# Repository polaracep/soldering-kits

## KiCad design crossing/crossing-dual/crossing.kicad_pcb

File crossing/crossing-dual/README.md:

## 2 Mode Level Crossing (přejezd) 

A level crossing sign. based on czech ažd-97. 

### Features 

- 2 selectable operational modes (changeable using solder bridges)
    1) the leds blinking alternately
    2) pad in the middle can be used as a button to turn the leds on
- can be soldered with smd or tht parts.
- a printable leg (M2 screws for mounting)
 
### Mounting

1. On top of the board is a hole for a lanyard/keychain.
2. In the folder `3D addons` are STLs for a leg and hoods for the LEDs. 
    - use an M2 screw
    - No nut is necessary, the leg is made to be a tight fit

### Circuit

[falstad link](https://tinyurl.com/22jwxxro)

the basic circuit is just a basic astable multivibrator with 2 leds. 

the second circuit bypasses the capacitors, instead using a resistive pad and a resistor divider, which pull both bases of the transistors high, thus turning led's on.

you don't need to solder every component for only one of the circuits to work. all parts are labeled with the numbers **1** or **2**, each corresponding to one of the circuits. you can then select the desired one using solder pads.

### Schematic

### PCB + dimensions

### BOM
| REF | CNT | NAME
| --- | ----- | -----
| BT1 | 1 | 2032 Holder
| C1, C2 | 2 | 47uF, 6.3x5
| D1, D2 | 2 | Red LED, 10mm
| Q1, Q2 | 2 | 2N3904, TO-92
| R1, R6 | 2 | 62k, 0207
| R2, R5 | 2 | 100R, 0207
| R3 | 1 | 1M, 0207
| R4 | 1 | 10k, 0207
| SW1 | 1 | 3-Pin, SPDT
| - | - | -
| SUM | 14 | 

#### Disclaimer 
I hereby give up all responsibility for the functionality of your boards.

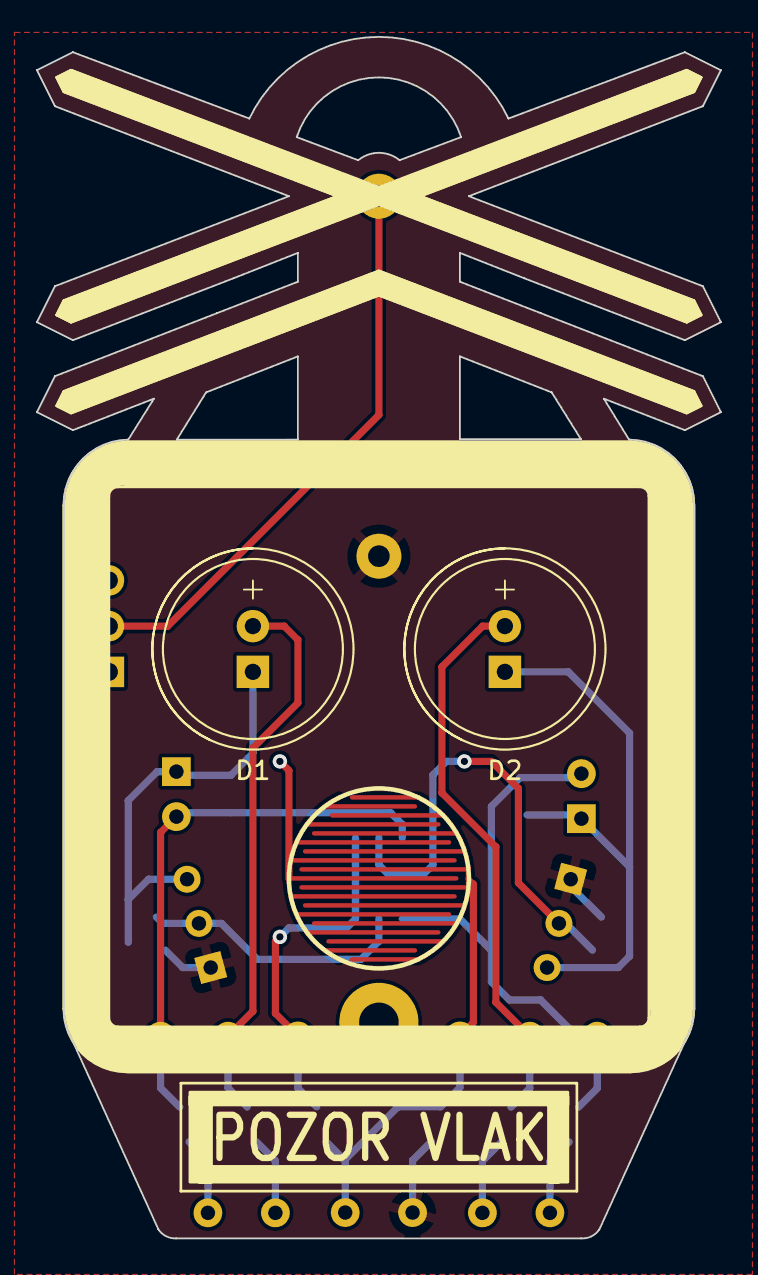
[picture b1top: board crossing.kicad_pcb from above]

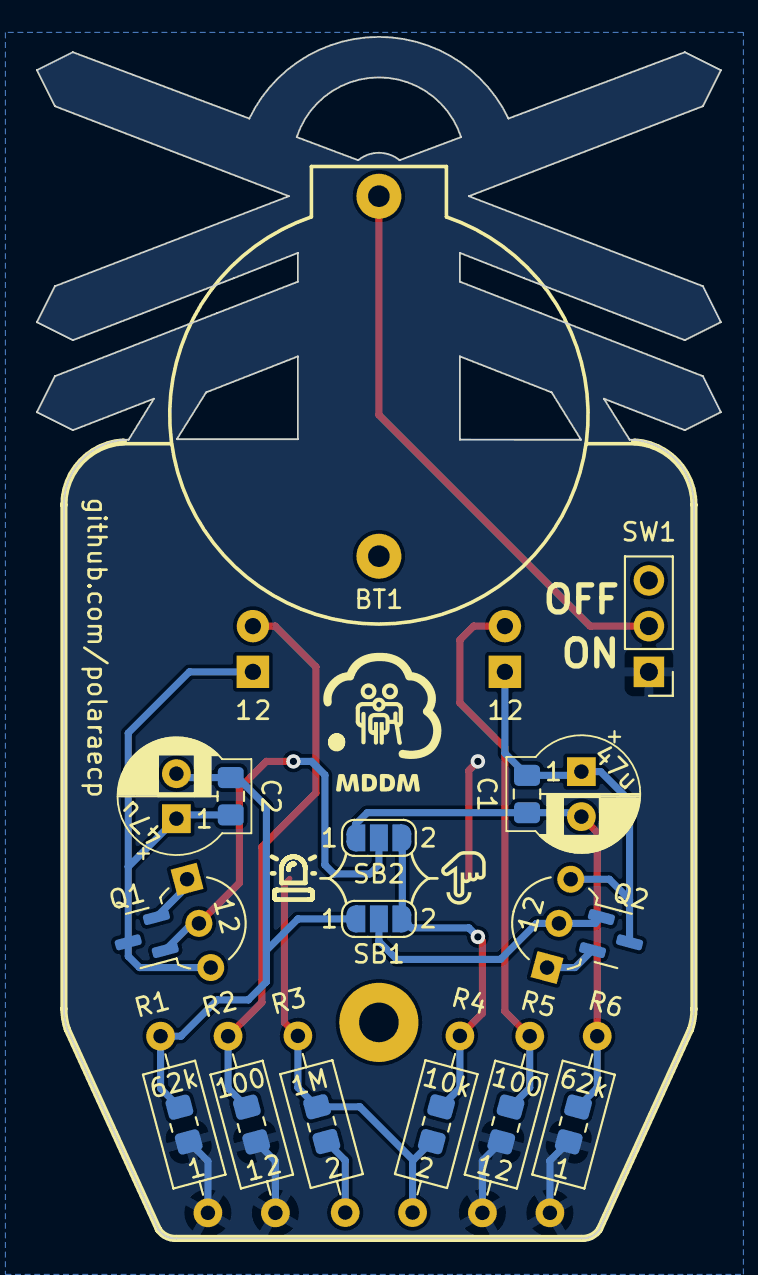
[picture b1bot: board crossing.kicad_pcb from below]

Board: 2 copper layers, 38.0 x 66.7 mm, 17 parts (14 on the bottom side), 13 nets.

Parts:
BT1: 3V; CONNFLY_DS1092-04
C1, C2: 47u; CP_Radial_D6.3mm_P2.50mm+SMD_0805
D1, D2: RED; LED_D10.0mm
J1: PAD; Touchpad_resistive
Q1, Q2: 2N3904; TO-92L_Inline_Wide+SMD_SOT-23
R1, R6: 62k; R_Axial_SMD_DIN0207_L6.3mm_D2.5mm_P10.16mm_Horizontal
R2, R5: 100R; R_Axial_SMD_DIN0207_L6.3mm_D2.5mm_P10.16mm_Horizontal
R3: 1M; R_Axial_SMD_DIN0207_L6.3mm_D2.5mm_P10.16mm_Horizontal
R4: 10k; R_Axial_SMD_DIN0207_L6.3mm_D2.5mm_P10.16mm_Horizontal
SB1, SB2: SolderJumper-3_P1.3mm_Open_RoundedPad1.0x1.5mm_NumberLabels
SW1: SW_SPDT; PinHeader_1x03_P2.54mm_Vertical

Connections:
+3.3V: J1.1, R1.1, R2.1, R5.1, R6.1, SW1.1 (A)
/TOUCH: R4.1, SB1.3 (B), SB2.3 (B)
GND: BT1.2 (-), Q1.1 (E), Q2.1 (E), R3.2
unnamed: BT1.1 (+), SW1.2 (B)
unnamed: D1.2 (A), R5.2
unnamed: C1.1, D1.1 (K), Q2.3 (C)
unnamed: D2.2 (A), R2.2
unnamed: C2.1, D2.1 (K), Q1.3 (C)
unnamed: J1.2, R3.1, R4.2
unnamed: Q1.2 (B), SB2.2 (C)
unnamed: Q2.2 (B), SB1.2 (C)
unnamed: C2.2, R1.2, SB1.1 (A)
unnamed: C1.2, R6.2, SB2.1 (A)
